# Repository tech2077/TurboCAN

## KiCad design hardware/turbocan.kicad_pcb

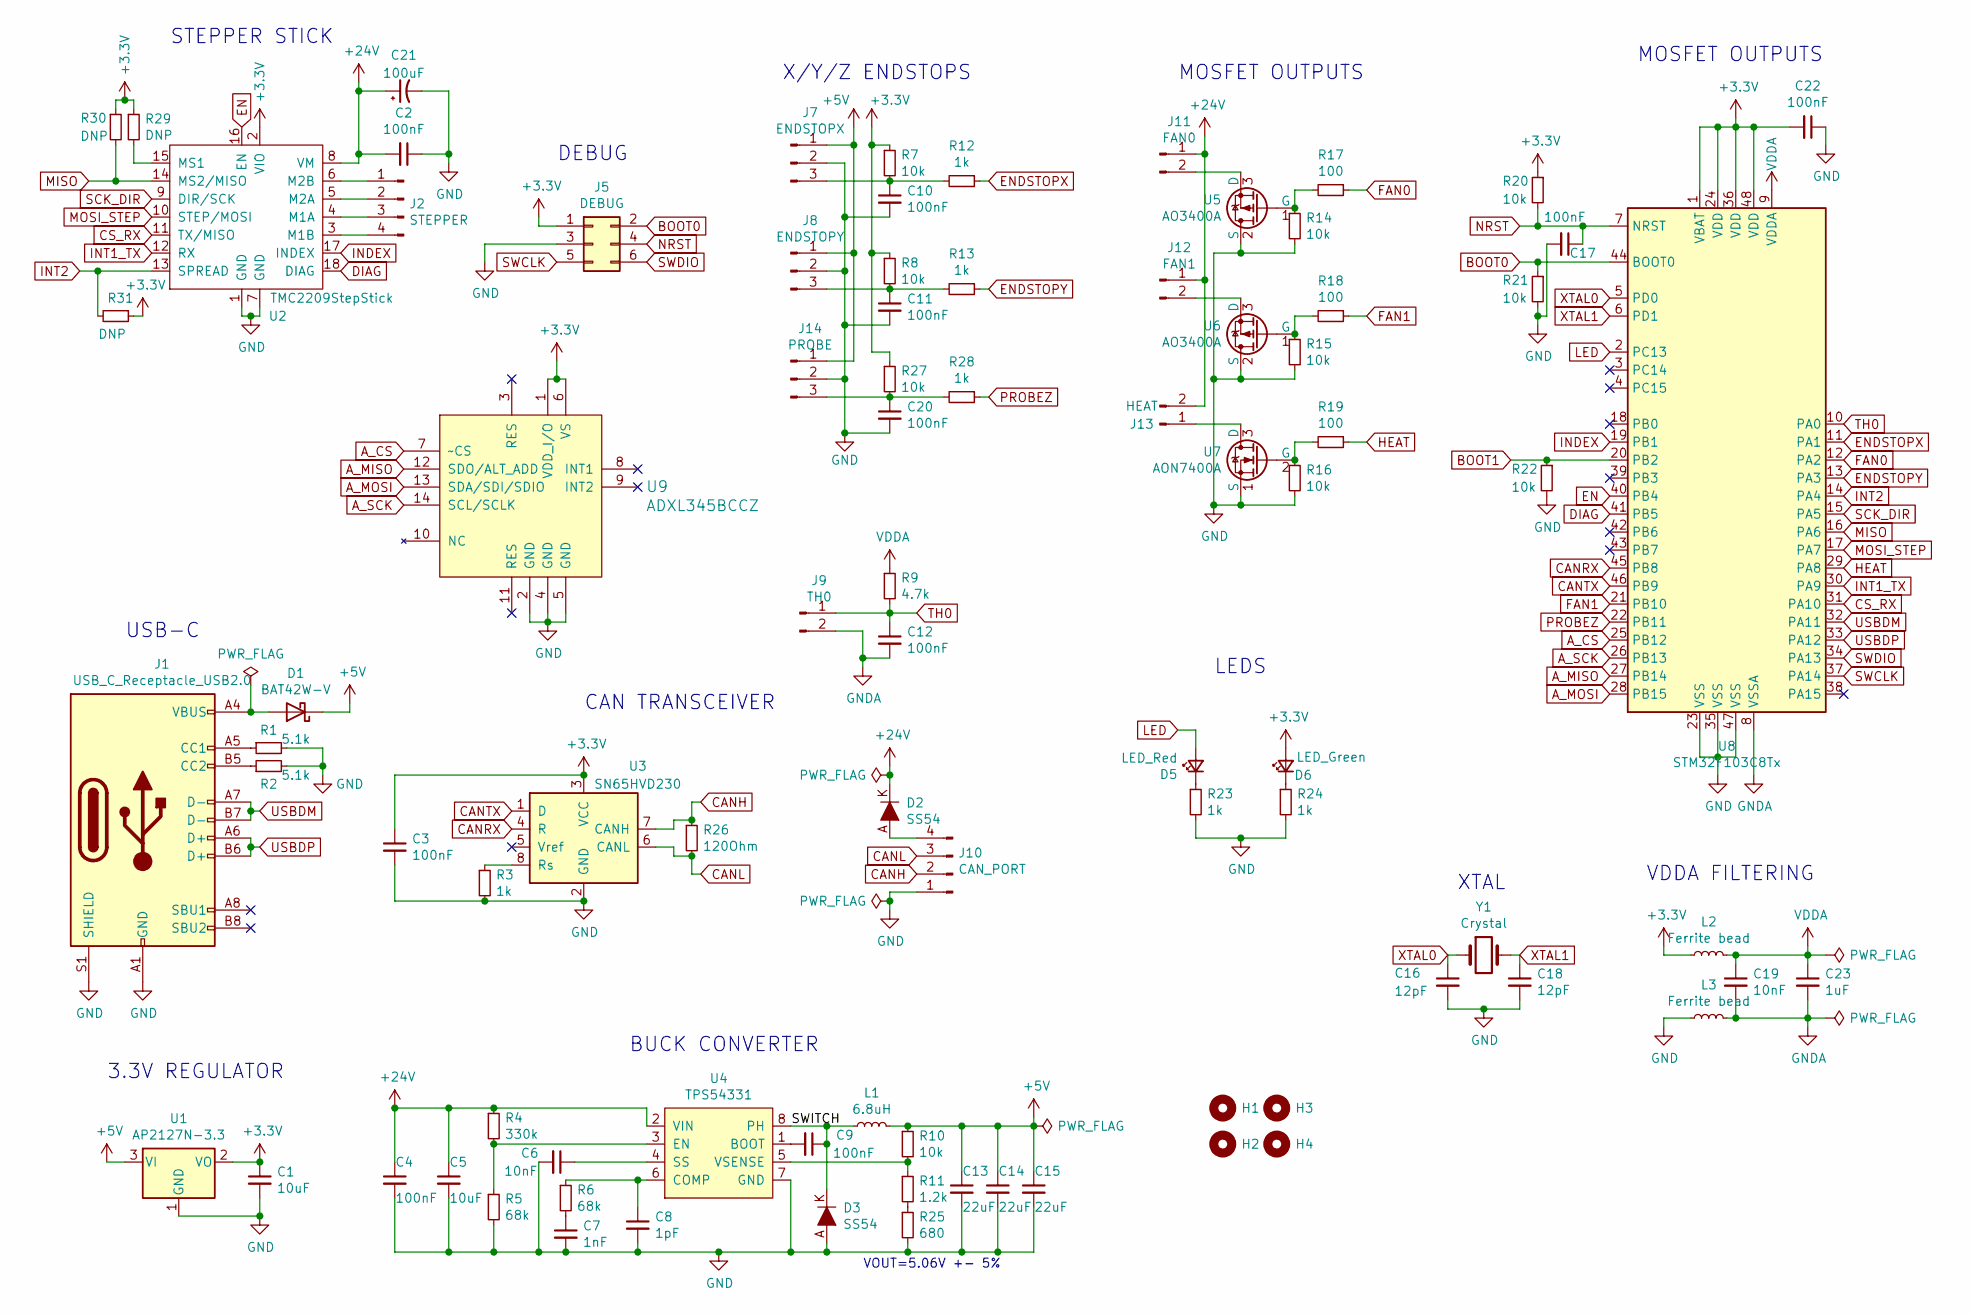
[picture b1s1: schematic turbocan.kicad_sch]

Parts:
C1, C5: 10uF; C_0805_2012Metric; LCSC Part Number C15850
C2, C3, C4, C9, C10, C11, C12, C17, C20, C22: 100nF; C_0402_1005Metric; LCSC Part Number C1525
C6, C19: 10nF; C_0402_1005Metric; LCSC Part Number C15195
C7: 1nF; C_0402_1005Metric; LCSC Part Number C1523
C8: 1pF; C_0402_1005Metric; LCSC Part Number C1550
C13, C14, C15: 22uF; C_0805_2012Metric; LCSC Part Number C45783
C16, C18: 12pF; C_0402_1005Metric; LCSC Part Number C1547
C21: 100uF; CP_Elec_8x10; LCSC Part Number C59944
C23: 1uF; C_0402_1005Metric; LCSC Part Number C52923
D1: BAT42W-V; D_SOD-123; LCSC Part Number C8598
D2, D3: SS54; DO-214AC; MPN SS14; Digi-Key_PN SS14CT-ND
D5: LED_Red; LED_0603_1608Metric; LCSC Part Number C2286
D6: LED_Green; LED_0603_1608Metric; LCSC Part Number C72043
H1, H2, H3, H4: MountingHole; MountingHole_3.2mm_M3_DIN965_Pad
J1: USB_C_Receptacle_USB2.0; USB_C_Receptacle_HRO_TYPE-C-31-M-12
J2: STEPPER; JST_XH_B4B-XH-A_1x04_P2.50mm_Vertical
J5: DEBUG; PinHeader_2x03_P2.54mm_Vertical
J7: ENDSTOPX; JST_XH_B3B-XH-A_1x03_P2.50mm_Vertical
J8: ENDSTOPY; JST_XH_B3B-XH-A_1x03_P2.50mm_Vertical
J9: TH0; JST_XH_B2B-XH-A_1x02_P2.50mm_Vertical
J10: CAN_PORT; JST_XH_B4B-XH-A_1x04_P2.50mm_Vertical
J11: FAN0; JST_XH_B2B-XH-A_1x02_P2.50mm_Vertical
J12: FAN1; JST_XH_B2B-XH-A_1x02_P2.50mm_Vertical
J13: HEAT; JST_XH_B2B-XH-A_1x02_P2.50mm_Vertical
J14: PROBE; JST_XH_B3B-XH-A_1x03_P2.50mm_Vertical
L1: 6.8uH; L_SMD_7.3x6.8; LCSC Part Number C207841
L2, L3: Ferrite bead; L_0805_2012Metric; LCSC Part Number C1017
R1, R2: 5.1k; R_0402_1005Metric; LCSC Part Number C25905
R3, R12, R13, R23, R24, R28: 1k; R_0402_1005Metric; LCSC Part Number C11702
R4: 330k; R_0402_1005Metric; LCSC Part Number C25778
R5, R6: 68k; R_0402_1005Metric; LCSC Part Number C36871
R7, R8, R10, R14, R15, R16, R20, R21, R22, R27: 10k; R_0402_1005Metric; LCSC Part Number C25744
R9: 4.7k; R_0805_2012Metric; LCSC Part Number C17673
R11: 1.2k; R_0402_1005Metric; LCSC Part Number C25862
R17, R18, R19: 100; R_0402_1005Metric; LCSC Part Number C25076
R25: 680; R_0402_1005Metric; LCSC Part Number C25130
R26: 120Ohm; R_0805_2012Metric; LCSC Part Number C17437
R29, R30, R31: DNP; R_0402_1005Metric
U1: AP2127N-3.3; SOT-23; LCSC Part Number C5446
U2: TMC2209StepStick
U3: SN65HVD230; SOIC-8_3.9x4.9mm_P1.27mm; LCSC Part Number C12084
U4: TPS54331; SOIC-8_3.9x4.9mm_P1.27mm; LCSC Part Number C9865
U5, U6: AO3400A; SOT-23; LCSC Part Number C344010
U7: AON7400A; DFN-8-1EP_3x3mm_P0.65mm_EP1.7x2.05mm_Thermal_Pad; LCSC Part Number C85734
U8: STM32F103C8Tx; LQFP-48_7x7mm_P0.5mm; LCSC Part Number C8734
U9: ADXL345BCCZ; LGA-14_3x5mm_RevA; MPN ADXL345BCCZ; Digi-Key_PN ADXL345BCCZ-ND
Y1: Crystal; Crystal_SMD_5032-2Pin_5.0x3.2mm; LCSC Part Number C115962

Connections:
+3V3: C1.1, C3.1, C22.2, D6.2 (A), J5.1, L2.1, R7.1, R8.1, R20.1, R27.1, R29.1, R30.1, R31.1, U1.2 (VO), U2.2 (VIO), U3.3 (VCC), U8.1 (VBAT), U8.24 (VDD), U8.36 (VDD), U8.48 (VDD), U9.1 (VDD_I/O), U9.6 (VS)
+5V: C13.1, C14.1, C15.1, D1.1 (K), J7.1, J8.1, J14.1, L1.2, R10.1, U1.3 (VI)
+24V: C2.2, C4.1, C5.1, C21.1, D2.K, J11.1, J12.1, J13.2, R4.1, U2.8 (VM), U4.2 (VIN)
/SWITCH: C9.1, D3.K, L1.1, U4.8 (PH)
A_CS: U8.25 (PB12), U9.7 (~CS)
A_MISO: U8.27 (PB14), U9.12 (SDO/ALT_ADD)
A_MOSI: U8.28 (PB15), U9.13 (SDA/SDI/SDIO)
A_SCK: U8.26 (PB13), U9.14 (SCL/SCLK)
BOOT0: J5.2, R21.1, U8.44 (BOOT0)
BOOT1: R22.1, U8.20 (PB2)
CANH: J10.2, R26.1, U3.7 (CANH)
CANL: J10.3, R26.2, U3.6 (CANL)
CANRX: U3.4 (R), U8.45 (PB8)
CANTX: U3.1 (D), U8.46 (PB9)
CS_RX: U2.11 (TX/MISO), U8.31 (PA10)
DIAG: U2.18 (DIAG), U8.41 (PB5)
EN: U2.16 (EN), U8.40 (PB4)
ENDSTOPX: R12.1, U8.11 (PA1)
ENDSTOPY: R13.1, U8.13 (PA3)
FAN0: R17.1, U8.12 (PA2)
FAN1: R18.1, U8.21 (PB10)
GND: C1.2, C2.1, C3.2, C4.2, C5.2, C6.2, C7.2, C8.2, C10.2, C11.2, C13.2, C14.2, C15.2, C16.2, C17.2, C18.2, C20.2, C21.2, C22.1, D3.A, J1.A1 (GND), J1.A12 (GND), J1.B1 (GND), J1.B12 (GND), J1.S1 (SHIELD), J5.3, J7.2, J8.2, J10.1, J14.2, L3.1, R1.2, R2.2, R3.2, R5.2, R14.2, R15.2, R16.2, R21.2, R22.2, R23.2, R24.2, R25.2, U1.1 (GND), U2.1 (GND), U2.7 (GND), U3.2 (GND), U4.7 (GND), U5.2 (S), U6.2 (S), U7.1 (S), U8.23 (VSS), U8.35 (VSS), U8.47 (VSS), U9.2 (GND), U9.4 (GND), U9.5 (GND)
GNDA: C12.2, C19.2, C23.2, J9.2, L3.2, U8.8 (VSSA)
HEAT: R19.1, U8.29 (PA8)
INDEX: U2.17 (INDEX), U8.19 (PB1)
INT1_TX: U2.12 (RX), U8.30 (PA9)
INT2: R31.2, U2.13 (SPREAD), U8.14 (PA4)
LED: D5.2 (A), U8.2 (PC13)
MISO: R30.2, U2.14 (MS2/MISO), U8.16 (PA6)
MOSI_STEP: U2.10 (STEP/MOSI), U8.17 (PA7)
NRST: C17.1, J5.4, R20.2, U8.7 (NRST)
unnamed: C6.1, U4.4 (SS)
unnamed: C7.1, R6.2
unnamed: C8.1, R6.1, U4.6 (COMP)
unnamed: C9.2, U4.1 (BOOT)
unnamed: C10.1, J7.3, R7.2, R12.2
unnamed: C11.1, J8.3, R8.2, R13.2
unnamed: C20.1, J14.3, R27.2, R28.2
unnamed: D1.2 (A), J1.A4 (VBUS), J1.A9 (VBUS), J1.B4 (VBUS), J1.B9 (VBUS)
unnamed: D2.A, J10.4
unnamed: D5.1 (K), R23.1
unnamed: D6.1 (K), R24.1
unnamed: J1.A5 (CC1), R1.1
unnamed: J1.B5 (CC2), R2.1
unnamed: J2.1, U2.6 (M2B)
unnamed: J2.2, U2.5 (M2A)
unnamed: J2.3, U2.4 (M1A)
unnamed: J2.4, U2.3 (M1B)
unnamed: J11.2, U5.3 (D)
unnamed: J12.2, U6.3 (D)
unnamed: J13.1, U7.3 (D)
unnamed: R3.1, U3.8 (Rs)
unnamed: R4.2, R5.1, U4.3 (EN)
unnamed: R10.2, R11.1, U4.5 (VSENSE)
unnamed: R11.2, R25.1
unnamed: R14.1, R17.2, U5.1 (G)
unnamed: R15.1, R18.2, U6.1 (G)
unnamed: R16.1, R19.2, U7.2 (G)
unnamed: R29.2, U2.15 (MS1)
PROBEZ: R28.1, U8.22 (PB11)
SCK_DIR: U2.9 (DIR/SCK), U8.15 (PA5)
SWCLK: J5.5, U8.37 (PA14)
SWDIO: J5.6, U8.34 (PA13)
TH0: C12.1, J9.1, R9.2, U8.10 (PA0)
USBDM: J1.A7 (D-), J1.B7 (D-), U8.32 (PA11)
USBDP: J1.A6 (D+), J1.B6 (D+), U8.33 (PA12)
VDDA: C19.1, C23.1, L2.2, R9.1, U8.9 (VDDA)
XTAL0: C16.1, U8.5 (PD0), Y1.1
XTAL1: C18.1, U8.6 (PD1), Y1.2

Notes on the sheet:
3.3V REGULATOR
USB-C
STEPPER STICK
DEBUG
CAN TRANSCEIVER
BUCK CONVERTER
X/Y/Z ENDSTOPS
VOUT=5.06V +- 5%
MOSFET OUTPUTS
LEDS
XTAL
VDDA FILTERING

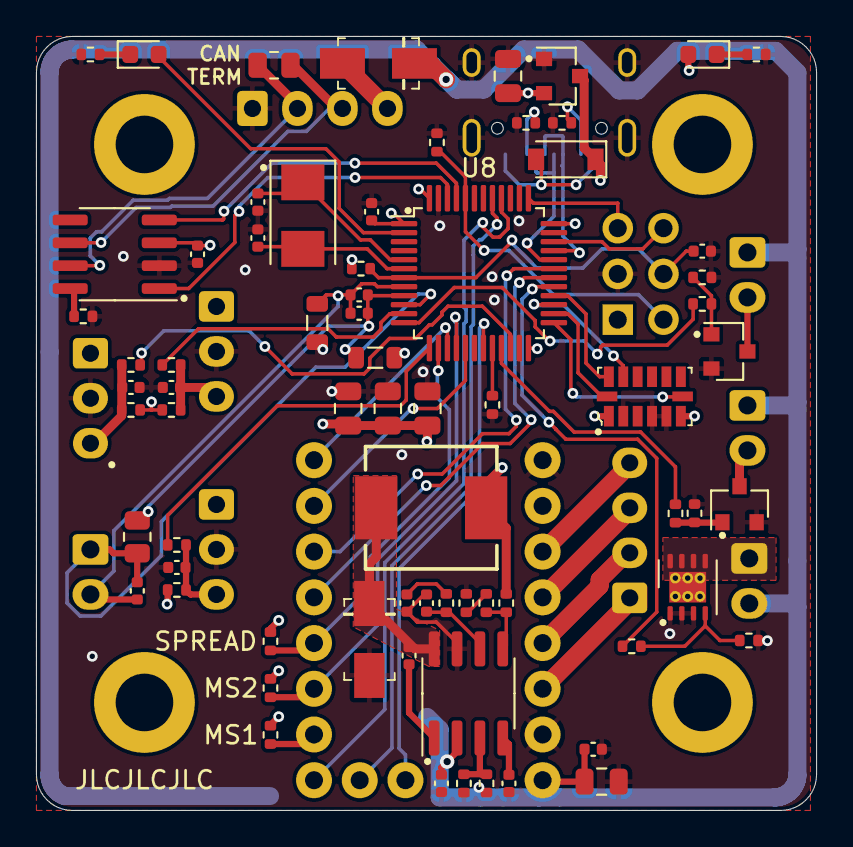
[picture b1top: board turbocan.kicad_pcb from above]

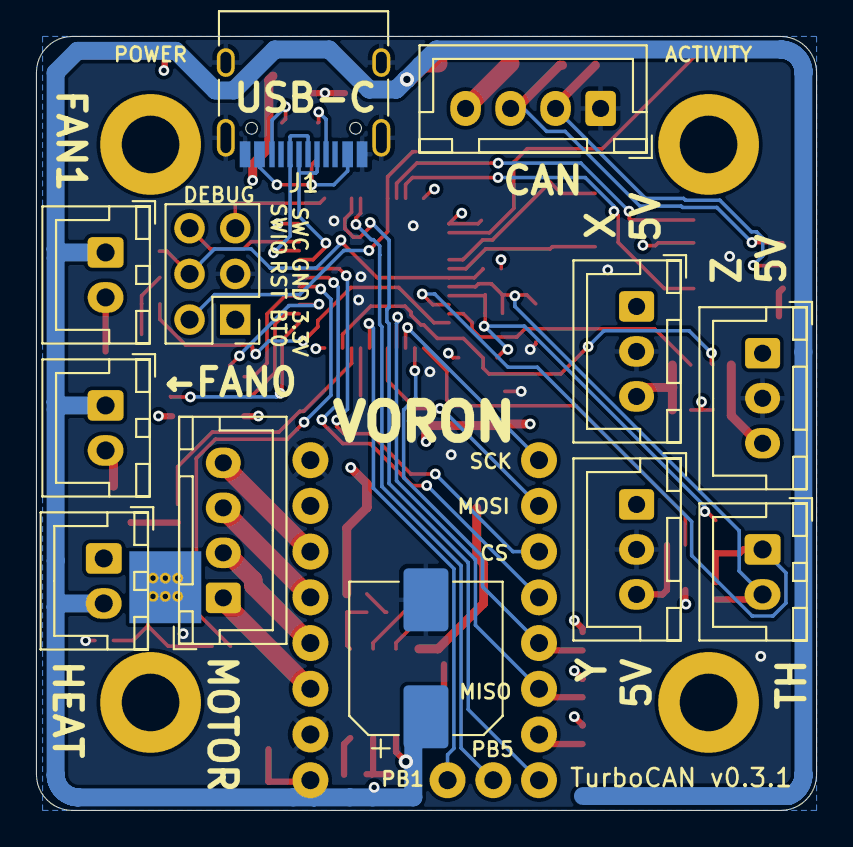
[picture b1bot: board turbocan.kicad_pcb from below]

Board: 4 copper layers, 43.3 x 43.0 mm, 87 parts (13 on the bottom side), 69 nets.

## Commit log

2021-08-13 Total reroute, move to 4 layer board, change mcu to more available stm32f103
